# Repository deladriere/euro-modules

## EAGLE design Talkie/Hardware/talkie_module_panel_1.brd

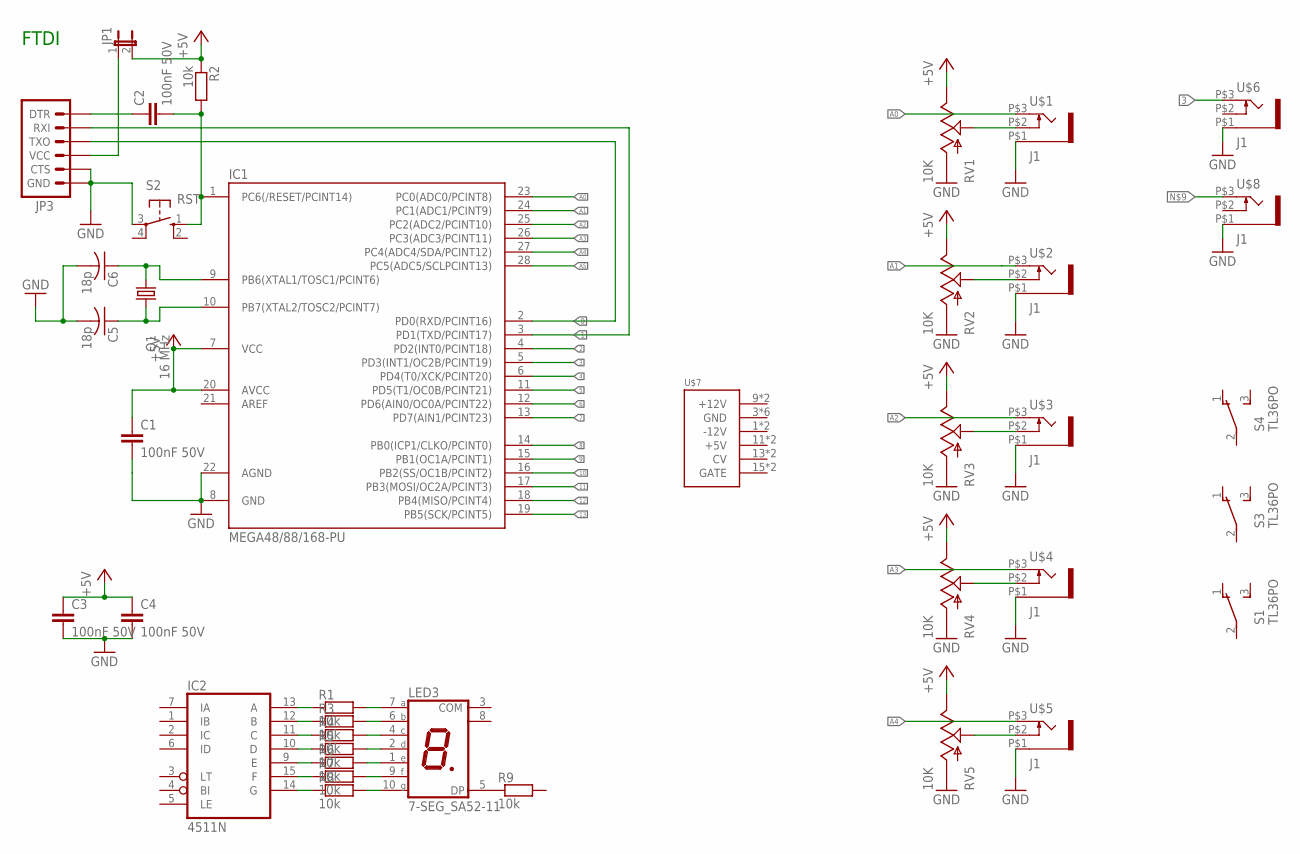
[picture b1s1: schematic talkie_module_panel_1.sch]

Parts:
C1, C2, C3, C4: 100nF 50V; C025-025X050
C5, C6: 18p; C025-025X050
IC1: MEGA48/88/168-PU; DIL28-3
IC2: 4511N; DIL16
JP1: JP1E; JP1
JP3: ARDUINO_SERIAL_PROGRAMLOCK; 1X06_LOCK
LED3: 7-SEG_SA52-11; SA52-11
Q1: 16 MHz; HC49/S
R1, R2, R3, R4, R5, R6, R7, R8, R9: 10k; RES-AXIAL-0.4
RV1, RV2, RV3, RV4, RV5: 10K; ALPS_POT
S1, S3, S4: TL36PO; TL3XPO
S2: RST; B3F-10XX
U$1, U$2, U$3, U$4, U$5, U$6, U$8: J1; THONKICONN
U$7: POWER; POWER_16

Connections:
0: IC1.2 (PD0(RXD/PCINT16)), JP3.3 (TXO)
1: IC1.3 (PD1(TXD/PCINT17)), JP3.2 (RXI)
2: IC1.4 (PD2(INT0/PCINT18))
3: IC1.5 (PD3(INT1/OC2B/PCINT19)), U$6.P$3 (3)
4: IC1.6 (PD4(T0/XCK/PCINT20))
5: IC1.11 (PD5(T1/OC0B/PCINT21))
6: IC1.12 (PD6(AIN0/OC0A/PCINT22))
7: IC1.13 (PD7(AIN1/PCINT23))
8: IC1.14 (PB0(ICP1/CLKO/PCINT0))
9: IC1.15 (PB1(OC1A/PCINT1))
10: IC1.16 (PB2(SS/OC1B/PCINT2))
11: IC1.17 (PB3(MOSI/OC2A/PCINT3))
12: IC1.18 (PB4(MISO/PCINT4))
13: IC1.19 (PB5(SCK/PCINT5))
+5V: C1.1, C3.1, C4.1, IC1.7 (VCC), IC1.20 (AVCC), JP1.2, R2.P$1 (1), RV1.P$1 (E), RV2.P$1 (E), RV3.P$1 (E), RV4.P$1 (E), RV5.P$1 (E)
A0: IC1.23 (PC0(ADC0/PCINT8)), U$1.P$3 (3)
A1: IC1.24 (PC1(ADC1/PCINT9)), U$2.P$3 (3)
A2: IC1.25 (PC2(ADC2/PCINT10)), U$3.P$3 (3)
A3: IC1.26 (PC3(ADC3/PCINT11)), U$4.P$3 (3)
A4: IC1.27 (PC4(ADC4/SDA/PCINT12)), U$5.P$3 (3)
A5: IC1.28 (PC5(ADC5/SCLPCINT13))
GND: C1.2, C3.2, C4.2, C5.2, C6.2, IC1.8 (GND), IC1.22 (AGND), JP3.5 (CTS), JP3.6 (GND), RV1.P$3 (A), RV2.P$3 (A), RV3.P$3 (A), RV4.P$3 (A), RV5.P$3 (A), S2.3, U$1.P$1 (5), U$2.P$1 (5), U$3.P$1 (5), U$4.P$1 (5), U$5.P$1 (5), U$6.P$1 (5), U$8.P$1 (5)
unnamed: RV1.P$2 (S), U$1.P$2 (4)
unnamed: RV2.P$2 (S), U$2.P$2 (4)
unnamed: C5.1, IC1.10 (PB7(XTAL2/TOSC2/PCINT7)), Q1.1
unnamed: JP1.1, JP3.4 (VCC)
unnamed: RV3.P$2 (S), U$3.P$2 (4)
unnamed: RV4.P$2 (S), U$4.P$2 (4)
unnamed: RV5.P$2 (S), U$5.P$2 (4)
unnamed: IC2.13 (A), R1.P$1 (1)
unnamed: LED3.7 (A), R1.P$2 (2)
unnamed: LED3.5 (DP), R9.P$1 (1)
unnamed: C6.1, IC1.9 (PB6(XTAL1/TOSC1/PCINT6)), Q1.2
unnamed: C2.2, IC1.1 (PC6(/RESET/PCINT14)), R2.P$2 (2), S2.1 (S)
unnamed: C2.1, JP3.1 (DTR)
unnamed: IC2.12 (B), R3.P$1 (1)
unnamed: LED3.6 (B), R3.P$2 (2)
unnamed: IC2.11 (C), R4.P$1 (1)
unnamed: LED3.4 (C), R4.P$2 (2)
unnamed: IC2.10 (D), R5.P$1 (1)
unnamed: LED3.2 (D), R5.P$2 (2)
unnamed: IC2.9 (E), R6.P$1 (1)
unnamed: LED3.1 (E), R6.P$2 (2)
unnamed: IC2.15 (F), R7.P$1 (1)
unnamed: LED3.9 (F), R7.P$2 (2)
unnamed: IC2.14 (G), R8.P$1 (1)
unnamed: LED3.10 (G), R8.P$2 (2)
VDD: IC2.16 (VDD)
VSS: IC2.8 (VSS)

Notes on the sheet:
FTDI

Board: 2 copper layers, 38 parts (0 on the bottom side), 35 nets, no tracks yet.

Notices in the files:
parts and their libraries:
SparkFun-Connectors: Licensing: CC v3.0 Share-Alike You are welcome to use this library for commercial purposes.
SparkFun-Electromechanical: Licensing: Creative Commons ShareAlike 4.0 International - https://creativecommons.org/licenses/by-sa/4.0
